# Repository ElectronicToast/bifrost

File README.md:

Arduino Nano RGB LED controller

## Description

Bifrost is an expansion board for the Arduino Nano v3.x for control of WS2811-based addressable RGB LED strips. Four LED outputs are provided for driving multiple strips; however, the RAM limitations of the ATmega328p must be kept in mind. A stereo audio jack and a socket for an [Adafruit MAX4466 electret microphone](https://www.adafruit.com/product/1063) are present for music visualization applications.

Four pushbuttons and three status LEDs onboard permit physical user control. If different peripherals are desired, an auxiliary connection header is provided for adding off-board I/O.

A socket for an HC-05 module is present, permitting serial communication and programming over Bluetooth. I2C connectors are provided for chaining multiple boards. A microSD card socket is also provided for storage of configuration settings, animations, etc.

This project is designed with KiCad EDA v.5.1.5. Documentation can be found under `/doc` and fabrication files under `/gerber`.

## Photos

## Usage
Connect DC power (7-12V recommended) to the VIN port. If LED output power is desired, connect external LED power to the VLED port. Do not attempt to draw more than 1-2A of current from any one LED output.

To power the board from the VLED input, bridge jumper JP1. 5V must be provided to VLED if JP1 is closed.

To use an HC-05 module for Bluetooth serial, bridge jumpers JP3 and JP4. Do not connect additional UART devices to the Arduino Nano hardware UART if the HC-05 is used. A 100 ohm resistor on JP3 is recommended to prevent TX bus contention. To enable Bluetooth programming, also bridge JP2.

## Author
- Ray Sun - Undergraduate, Electrical Engineering, Caltech, Class of 2020

## Licensing
This project is released under the terms of the MIT License.

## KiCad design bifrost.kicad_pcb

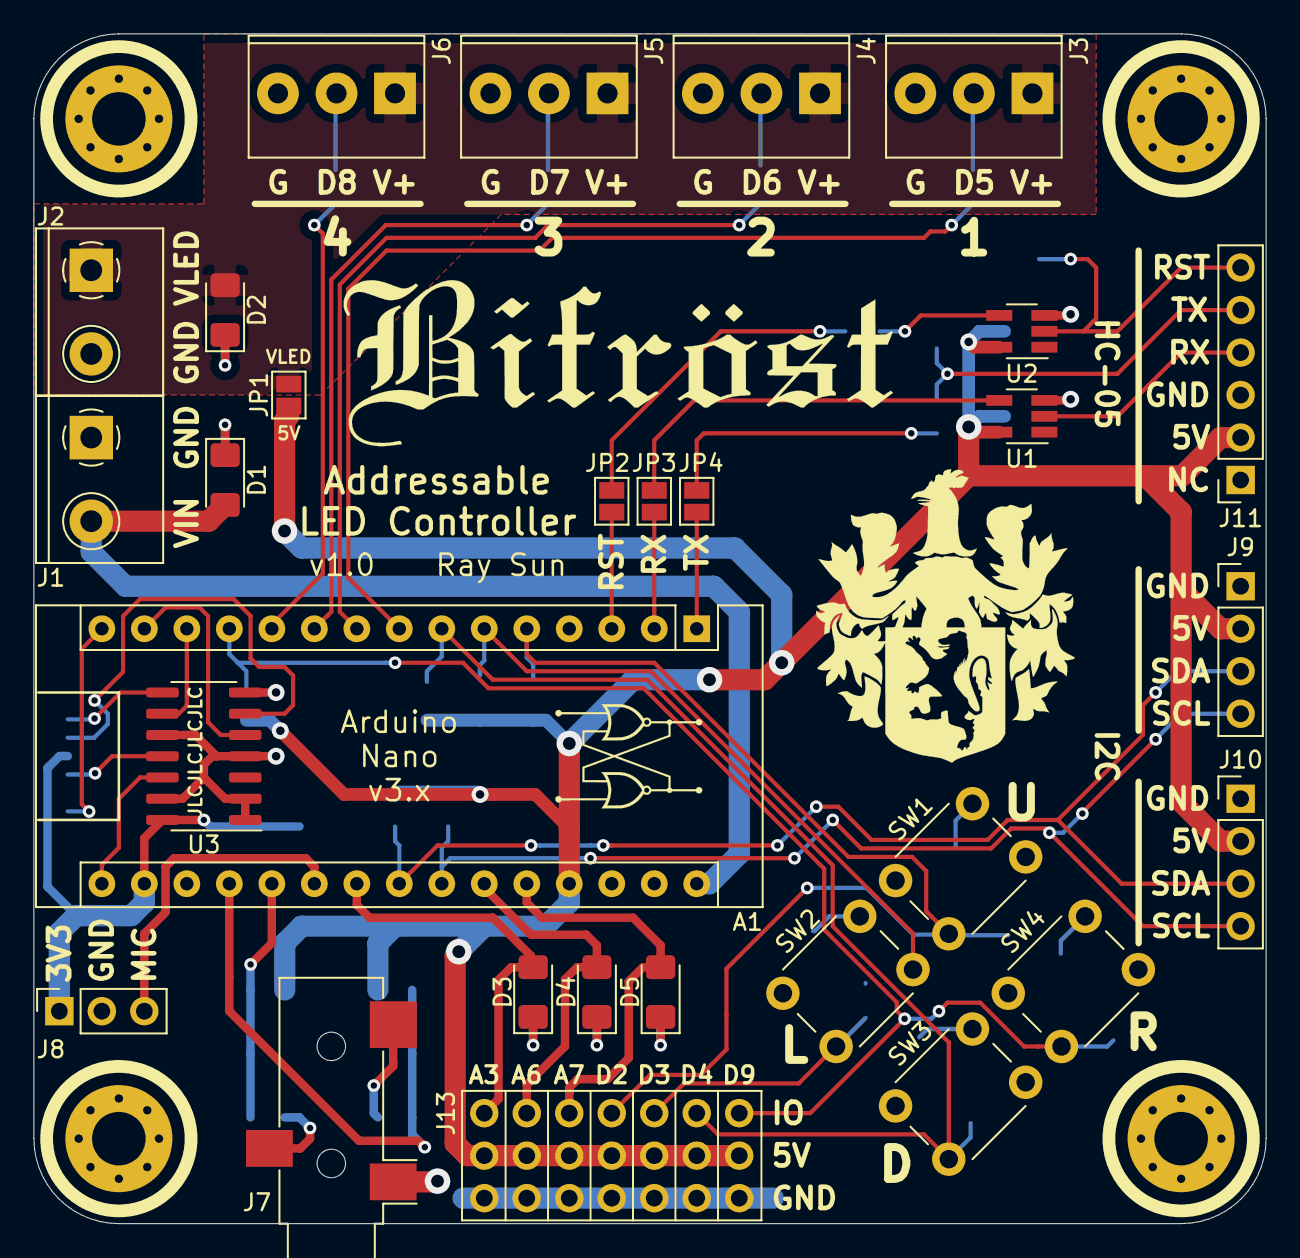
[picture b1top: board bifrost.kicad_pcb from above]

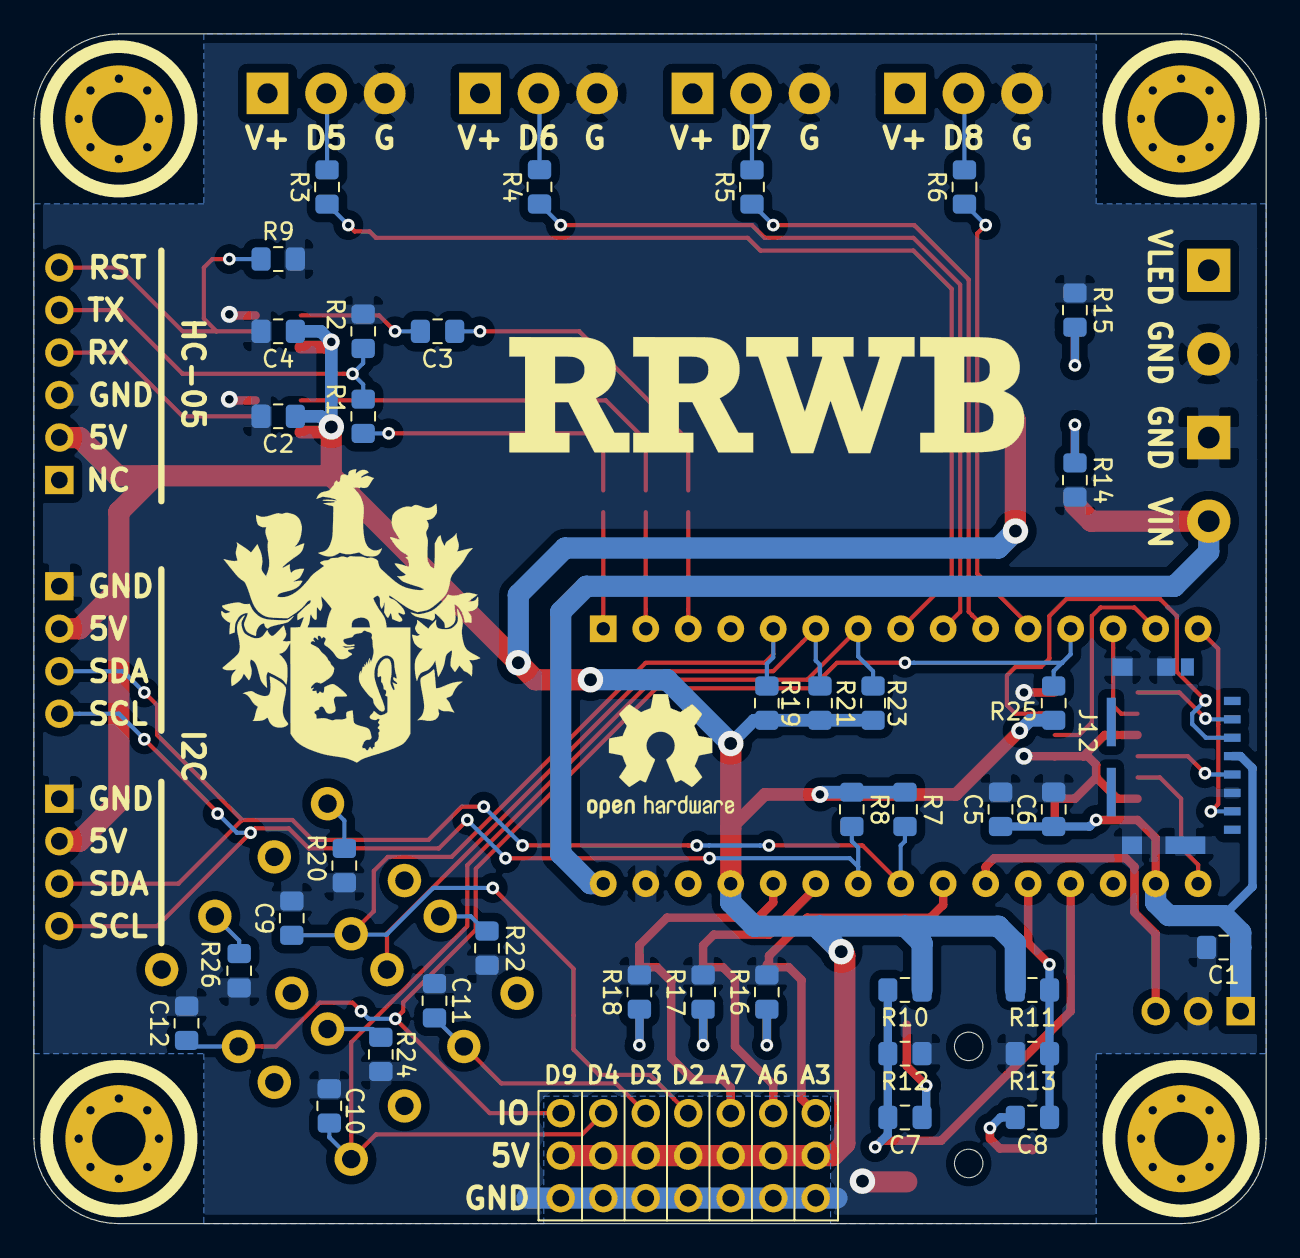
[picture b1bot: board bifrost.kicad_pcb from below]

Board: 2 copper layers, 73.7 x 71.1 mm, 72 parts (39 on the bottom side), 53 nets.

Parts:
A1: Arduino_Nano_v3.x; Arduino_Nano
C1, C2, C3, C4, C6, C9, C10, C11, C12: 0.1uF; C_0805_2012Metric_Pad1.15x1.40mm_HandSolder
C5: 1uF; C_0805_2012Metric_Pad1.15x1.40mm_HandSolder
C7, C8: 10uF; C_0805_2012Metric_Pad1.15x1.40mm_HandSolder
D1: RED; LED_1206_3216Metric_Pad1.42x1.75mm_HandSolder
D2: GRN; LED_1206_3216Metric_Pad1.42x1.75mm_HandSolder
D3, D4, D5: BLU; LED_1206_3216Metric_Pad1.42x1.75mm_HandSolder
H1, H2, H3, H4: M3; MountingHole_3.2mm_M3_Pad_Via
J1, J2: 395430002; TerminalBlock_Molex_395430602_1x02_P5.00mm_Horizontal
J3, J4, J5, J6: 393570003; TerminalBlock_Molex_393570003_1x03_P3.50mm_Horizontal
J7: SJ_3524; Jack_3.5mm_CUI_SJ-3523-SMT_Horizontal
J8: Conn_0.1_01x03; PinSocket_1x03_P2.54mm_Vertical
J9, J10: Conn_0.1_01x04; PinHeader_1x04_P2.54mm_Vertical
J11: Conn_0.1_01x06; PinSocket_1x06_P2.54mm_Vertical
J12: Micro_SD_Card_Det_Single; microSD_Molex_1051620001
J13: Conn_03x07_23_Common; PinHeader_03x07_P2.54mm_Vertical
JP1, JP2, JP3, JP4: SolderJumper_2_Open; SolderJumper-2_P1.3mm_Open_Pad1.0x1.5mm
R1, R14: 1K; R_0805_2012Metric_Pad1.15x1.40mm_HandSolder
R2: 2K; R_0805_2012Metric_Pad1.15x1.40mm_HandSolder
R3, R4, R5, R6, R15, R16, R17, R18: 330; R_0805_2012Metric_Pad1.15x1.40mm_HandSolder
R7, R8: 4.7K; R_0805_2012Metric_Pad1.15x1.40mm_HandSolder
R9, R19, R21, R23, R25: 10K; R_0805_2012Metric_Pad1.15x1.40mm_HandSolder
R10, R11, R12, R13: 100K; R_0805_2012Metric_Pad1.15x1.40mm_HandSolder
R20, R22, R24, R26: 100; R_0805_2012Metric_Pad1.15x1.40mm_HandSolder
SW1, SW2, SW3, SW4: SW_Push; SW_PUSH_6mm_H5mm
U1: 74LVC1G17; SOT-23-5_HandSoldering
U2: 74LVC1G14; SOT-23-5_HandSoldering
U3: 74AHCT125; SOIC-14_3.9x8.7mm_P1.27mm

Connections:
+3V3: A1.17, C1.1, C5.1, C6.1, J8.1, J12.4, U3.14
+5V: A1.27, C2.1, C4.1, J9.2, J10.2, J11.2, J13.8, J13.9, J13.10, J13.11, J13.12, J13.13, J13.14, JP1.2, R7.1, R8.1, R10.1, R11.1, R19.1, R21.1, R23.1, R25.1, U1.5, U2.5
/AUD_IN_L: C7.2, J7.T
/AUD_IN_R: C8.2, J7.R
/AUD_L: A1.19, C7.1, R10.2, R12.1
/AUD_R: A1.20, C8.1, R11.2, R13.1
/BTN1: A1.5, C9.1, J13.4, R19.2, SW1.2
/BTN2: A1.6, C11.1, J13.3, R21.2, SW2.2
/BTN3: A1.7, C10.1, J13.2, R23.2, SW3.2
/BTN4: A1.12, C12.1, J13.1, R25.2, SW4.2
/BT_RST: C3.1, JP2.2
/BT_RX: J11.5, R1.2, R2.1
/BT_ST: J11.6, R9.1, U2.2
/BT_TX: J11.4, U1.2
/I2C_SCL: A1.24, J9.4, J10.4, R8.2
/I2C_SDA: A1.23, J9.3, J10.3, R7.2
/LED1: A1.22, D3.2, J13.7
/LED2: A1.25, D4.2, J13.6
/LED3: A1.26, D5.2, J13.5
/MIC_IN: A1.21, J8.3
/MISO: A1.15, J12.7
/MOSI: A1.14, U3.5
/OUT1: J3.2, R3.2
/OUT2: J4.2, R4.2
/OUT3: J5.2, R5.2
/OUT4: J6.2, R6.2
/SCK: A1.16, U3.12
/~CS: A1.13, U3.9
GND: A1.29, C1.2, C2.2, C4.2, C5.2, C6.2, C9.2, C10.2, C11.2, C12.2, J1.1, J2.2, J3.3, J4.3, J5.3, J6.3, J7.S, J8.2, J9.1, J10.1, J11.3, J12.6, J12.10, J13.15, J13.16, J13.17, J13.18, J13.19, J13.20, J13.21, R2.2, R9.2, R12.2, R13.2, R14.2, R15.2, R16.2, R17.2, R18.2, R20.2, R22.2, R24.2, R26.2, U1.3, U2.3, U3.1, U3.2, U3.4, U3.7, U3.10, U3.13
unnamed: A1.1, JP4.1
unnamed: A1.2, JP3.1
unnamed: A1.3, JP2.1
unnamed: A1.8, R3.1
unnamed: A1.9, R4.1
unnamed: A1.10, R5.1
unnamed: A1.11, R6.1
unnamed: C3.2, U2.4
unnamed: D1.1, R14.1
unnamed: D2.1, R15.1
unnamed: D3.1, R16.1
unnamed: D4.1, R17.1
unnamed: D5.1, R18.1
unnamed: J12.2, U3.8
unnamed: J12.3, U3.6
unnamed: J12.5, U3.11
unnamed: JP3.2, U1.4
unnamed: JP4.2, R1.1
unnamed: R20.1, SW1.1
unnamed: R22.1, SW2.1
unnamed: R24.1, SW3.1
unnamed: R26.1, SW4.1
VBUS: A1.30, D1.2, J1.2
VDD: D2.2, J2.1, J3.1, J4.1, J5.1, J6.1, JP1.1

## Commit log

2019-12-17 Create project
2019-12-18 Make schematic
2019-12-18 Split LED power bus in half, for more current capability
2019-12-18 Fix HC-05 interface
2019-12-18 Correct ground domain connection to MCU power input
2019-12-20 Select buttons and terminal blocks
2019-12-20 Make terminal block footprints
2019-12-20 Add in terminal block footprints and some additional comments
2019-12-20 Select output capacitors (might not be necessary)
2019-12-20 Fix indicators
2019-12-20 Add more comments
2019-12-21 Add termination resistors to outputs
2019-12-21 Add second I2C connector for easier connection of multiple boards
2019-12-23 Move project files to main directory
2019-12-23 Footprint for HC-05 and I2C connectors need update
2019-12-23 Add cap to couple Bluetooth reset signal
2019-12-23 Begin PCB layout
2019-12-25 Free up SPI pins for possible SD card
2019-12-27 Remove LED power inputs and simplify schematic
2019-12-27 Add microSD socket and footprint
2019-12-27 Add microSD socket and buffer IC
2019-12-27 Add a buffer to HC-05 TX line to win contention with CH340 on Nano
2019-12-27 Replace reset MOSFET with inverter IC
2019-12-27 Revise comments
2019-12-27 Move things around
2019-12-27 Select terminal blocks (need footprints)
2019-12-27 Replace solder jumpers with THT jumpers for easier swap between wireless and USB serial
2019-12-27 Fix disconnected nets
2019-12-28 Add jumper to disconnect 5V power input from Nano
2019-12-28 Add redundant pulldown to HC-05 reset
2019-12-28 Flip status LED and resistor order for easier layout
2019-12-28 Update 2 and 3 pin Molex 3954306xx 5mm pitch footprints
2019-12-28 Make Molex 3935700xx 3.5mm pitch footprints
2019-12-28 Assign remaining footprints
2019-12-28 Change status LED resistor values to cut down on different resistance values
2019-12-28 Add a separate VIN indicator
2019-12-29 Begin placement
2020-01-04 Fix J11 footprint assignment and switch VIN pinout
2020-01-04 Do most placement
2020-01-04 Move some footprints and designators around
2020-01-04 Fully split power domains
2020-01-04 Start labelling conector pins
2020-01-04 Continue labelling and start routing
2020-01-04 Change 5V indicator to external LED power indicator
2020-01-04 Remap 74AHCT125 buffer for easier routing
2020-01-04 Continue routing
2020-01-04 Renumber switches
2020-01-04 Switch pin jumpers to solder jumpers to reduce part count
2020-01-04 Add project logos and footprints
2020-01-04 Finish most routing
2020-01-04 Move logos around
2020-01-04 Clean up
2020-01-04 Move refdes around
2020-01-04 Make 03x07 pin header symbol and footprint for auxiliary I/O connector
2020-01-04 Change label
2020-01-04 Change symbol to connect all common
2020-01-04 Place aux I/O connector on PCB
2020-01-05 Complete routing
2020-01-05 Snap some traces to pads
2020-01-05 Edit footprint silk and add pin labels
2020-01-09 Check for fabrication
2020-01-09 Generate Gerbers for production
2020-01-09 Generate schematic and fabrication prints
2020-01-09 Add board renders
2020-01-10 Replace 74AHCT125 with 3V3-compatible equivalent 74LVC125
2020-02-06 Generate stencil PDFs
2020-02-15 Add 2x scale fabrication prints
2020-02-24 Add dimensions
2020-02-24 Add bumper 3D print to protect exposed underside pins
2020-03-10 Make bumper thicker for sturdier 3D printing (3 x 0.4mm)
2020-12-25 Update logo
2021-01-26 Add library tables
2021-01-26 Add 3d model references
2021-01-26 Add new renders
2021-01-26 Fix image filename case
